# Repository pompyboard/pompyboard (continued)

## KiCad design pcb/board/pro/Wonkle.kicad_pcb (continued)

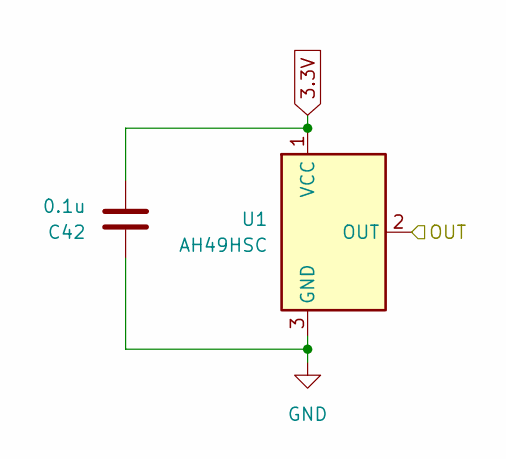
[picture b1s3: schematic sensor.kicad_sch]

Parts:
C42: 0.1u; C_0402_1005Metric; LCSC Part # C1525
U1: AH49HSC; SOT-23-3; LCSC Part # C510723

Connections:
3.3V: C42.2, U1.1 (VCC); also elsewhere on the board
/sensor column0/sensor0/OUT: U1.2 (OUT); also elsewhere on the board
GND: C42.1, U1.3 (GND); also elsewhere on the board

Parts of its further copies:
C43, C44, C45, C46, C47, C48, C49, C50, C51, C52, C53, C54, C55, C56, C57, C58, C59, C60, C61, C62, C63, C64, C65, C66, C67, C68, C69, C70, C71, C72, C73, C74, C75, C76, C77, C78, C79, C80, C81, C82, C83, C84, C85, C86, C87, C88, C89, C90, C91, C92, C93, C94, C95, C96, C97, C98, C99, C100, C101, C102, C103, C104, C105, C106, C107, C108, C109, C110, C111, C112, C113, C114, C115, C116, C117, C118, C119, C120, C121, C122, C123, C124, C125, C126, C127, C128, C129, C130, C131, C132, C133, C134, C135, C136, C137, C138, C139, C140, C141, C142, C143, C144, C145, C146, C147, C148, C149, C150, C151, C152, C153, C154, C155, C156, C157, C158, C159, C160, C161, C162, C163, C164, C165, C166, C167, C168, C169, C170, C171, C172, C173, C174, C175, C176, C177, C178, C179, C180, C181, C182, C183, C184, C185, C186, C187, C188, C189, C190, C191, C192, C193, C194, C195, C196, C197, C198, C199, C200, C201, C202, C203, C204, C205, C206, C207, C208, C209, C210, C211, C212, C213, C214, C215, C216, C217, C218, C219, C220, C221, C222, C223, C224, C225, C226, C227, C228, C229, C230, C231, C232, C233, C234, C235, C236, C237, C238, C239, C240, C241, C242, C243, C244, C245, C246, C247, C248, C249, C250: 0.1u; C_0402_1005Metric; LCSC Part # C1525
U2, U3, U4, U5, U6, U7, U8, U9, U10, U11, U12, U13, U14, U15, U16, U17, U18, U19, U20, U21, U22, U23, U24, U25, U26, U27, U28, U29, U30, U31, U32, U33, U34, U35, U36, U37, U38, U39, U40, U41, U42, U43, U44, U45, U46, U47, U48, U49, U50, U51, U52, U53, U54, U55, U56, U57, U58, U59, U60, U61, U62, U63, U64, U65, U66, U67, U68, U69, U70, U71, U72, U73, U74, U75, U76, U77, U78, U79, U80, U81, U82, U83, U84, U85, U86, U87, U88, U89, U90, U91, U92, U93, U94, U95, U96, U97, U98, U99, U100, U101, U102, U103, U104, U105, U106, U107, U108, U109, U110, U111, U112, U113, U114, U115, U116, U117, U118, U119, U120, U121, U122, U123, U124, U125, U126, U127, U128, U129, U130, U131, U132, U133, U134, U135, U136, U137, U138, U139, U140, U141, U142, U143, U144, U145, U146, U147, U148, U149, U150, U151, U152, U153, U154, U155, U156, U157, U158, U159, U160, U161, U162, U163, U164, U165, U166, U167, U168, U169, U170, U171, U172, U173, U174, U175, U176, U177, U178, U179, U180, U181, U182, U183, U184, U185, U186, U187, U188, U189, U190, U191, U192, U193, U194, U195, U196, U197, U198, U199, U200, U201, U202, U203, U204, U205, U206, U207, U208, U209: AH49HSC; SOT-23-3; LCSC Part # C510723

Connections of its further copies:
3.3V: C43.2, C44.2, C45.2, C46.2, C47.2, C48.2, C49.2, C50.2, C51.2, C52.2, C53.2, C54.2, C55.2, C56.2, C57.2, C58.2, C59.2, C60.2, C61.2, C62.2, C63.2, C64.2, C65.2, C66.2, C67.2, C68.2, C69.2, C70.2, C71.2, C72.2, C73.2, C74.2, C75.2, C76.2, C77.2, C78.2, C79.2, C80.2, C81.2, C82.2, C83.2, C84.2, C85.2, C86.2, C87.2, C88.2, C89.2, C90.2, C91.2, C92.2, C93.2, C94.2, C95.2, C96.2, C97.2, C98.2, C99.2, C100.2, C101.2, C102.2, C103.2, C104.2, C105.2, C106.2, C107.2, C108.2, C109.2, C110.2, C111.2, C112.2, C113.2, C114.2, C115.2, C116.2, C117.2, C118.2, C119.2, C120.2, C121.2, C122.2, C123.2, C124.2, C125.2, C126.2, C127.2, C128.2, C129.2, C130.2, C131.2, C132.2, C133.2, C134.2, C135.2, C136.2, C137.2, C138.2, C139.2, C140.2, C141.2, C142.2, C143.2, C144.2, C145.2, C146.2, C147.2, C148.2, C149.2, C150.2, C151.2, C152.2, C153.2, C154.2, C155.2, C156.2, C157.2, C158.2, C159.2, C160.2, C161.2, C162.2, C163.2, C164.2, C165.2, C166.2, C167.2, C168.2, C169.2, C170.2, C171.2, C172.2, C173.2, C174.2, C175.2, C176.2, C177.2, C178.2, C179.2, C180.2, C181.2, C182.2, C183.2, C184.2, C185.2, C186.2, C187.2, C188.2, C189.2, C190.2, C191.2, C192.2, C193.2, C194.2, C195.2, C196.2, C197.2, C198.2, C199.2, C200.2, C201.2, C202.2, C203.2, C204.2, C205.2, C206.2, C207.2, C208.2, C209.2, C210.2, C211.2, C212.2, C213.2, C214.2, C215.2, C216.2, C217.2, C218.2, C219.2, C220.2, C221.2, C222.2, C223.2, C224.2, C225.2, C226.2, C227.2, C228.2, C229.2, C230.2, C231.2, C232.2, C233.2, C234.2, C235.2, C236.2, C237.2, C238.2, C239.2, C240.2, C241.2, C242.2, C243.2, C244.2, C245.2, C246.2, C247.2, C248.2, C249.2, C250.2, U2.1 (VCC), U3.1 (VCC), U4.1 (VCC), U5.1 (VCC), U6.1 (VCC), U7.1 (VCC), U8.1 (VCC), U9.1 (VCC), U10.1 (VCC), U11.1 (VCC), U12.1 (VCC), U13.1 (VCC), U14.1 (VCC), U15.1 (VCC), U16.1 (VCC), U17.1 (VCC), U18.1 (VCC), U19.1 (VCC), U20.1 (VCC), U21.1 (VCC), U22.1 (VCC), U23.1 (VCC), U24.1 (VCC), U25.1 (VCC), U26.1 (VCC), U27.1 (VCC), U28.1 (VCC), U29.1 (VCC), U30.1 (VCC), U31.1 (VCC), U32.1 (VCC), U33.1 (VCC), U34.1 (VCC), U35.1 (VCC), U36.1 (VCC), U37.1 (VCC), U38.1 (VCC), U39.1 (VCC), U40.1 (VCC), U41.1 (VCC), U42.1 (VCC), U43.1 (VCC), U44.1 (VCC), U45.1 (VCC), U46.1 (VCC), U47.1 (VCC), U48.1 (VCC), U49.1 (VCC), U50.1 (VCC), U51.1 (VCC), U52.1 (VCC), U53.1 (VCC), U54.1 (VCC), U55.1 (VCC), U56.1 (VCC), U57.1 (VCC), U58.1 (VCC), U59.1 (VCC), U60.1 (VCC), U61.1 (VCC), U62.1 (VCC), U63.1 (VCC), U64.1 (VCC), U65.1 (VCC), U66.1 (VCC), U67.1 (VCC), U68.1 (VCC), U69.1 (VCC), U70.1 (VCC), U71.1 (VCC), U72.1 (VCC), U73.1 (VCC), U74.1 (VCC), U75.1 (VCC), U76.1 (VCC), U77.1 (VCC), U78.1 (VCC), U79.1 (VCC), U80.1 (VCC), U81.1 (VCC), U82.1 (VCC), U83.1 (VCC), U84.1 (VCC), U85.1 (VCC), U86.1 (VCC), U87.1 (VCC), U88.1 (VCC), U89.1 (VCC), U90.1 (VCC), U91.1 (VCC), U92.1 (VCC), U93.1 (VCC), U94.1 (VCC), U95.1 (VCC), U96.1 (VCC), U97.1 (VCC), U98.1 (VCC), U99.1 (VCC), U100.1 (VCC), U101.1 (VCC), U102.1 (VCC), U103.1 (VCC), U104.1 (VCC), U105.1 (VCC), U106.1 (VCC), U107.1 (VCC), U108.1 (VCC), U109.1 (VCC), U110.1 (VCC), U111.1 (VCC), U112.1 (VCC), U113.1 (VCC), U114.1 (VCC), U115.1 (VCC), U116.1 (VCC), U117.1 (VCC), U118.1 (VCC), U119.1 (VCC), U120.1 (VCC), U121.1 (VCC), U122.1 (VCC), U123.1 (VCC), U124.1 (VCC), U125.1 (VCC), U126.1 (VCC), U127.1 (VCC), U128.1 (VCC), U129.1 (VCC), U130.1 (VCC), U131.1 (VCC), U132.1 (VCC), U133.1 (VCC), U134.1 (VCC), U135.1 (VCC), U136.1 (VCC), U137.1 (VCC), U138.1 (VCC), U139.1 (VCC), U140.1 (VCC), U141.1 (VCC), U142.1 (VCC), U143.1 (VCC), U144.1 (VCC), U145.1 (VCC), U146.1 (VCC), U147.1 (VCC), U148.1 (VCC), U149.1 (VCC), U150.1 (VCC), U151.1 (VCC), U152.1 (VCC), U153.1 (VCC), U154.1 (VCC), U155.1 (VCC), U156.1 (VCC), U157.1 (VCC), U158.1 (VCC), U159.1 (VCC), U160.1 (VCC), U161.1 (VCC), U162.1 (VCC), U163.1 (VCC), U164.1 (VCC), U165.1 (VCC), U166.1 (VCC), U167.1 (VCC), U168.1 (VCC), U169.1 (VCC), U170.1 (VCC), U171.1 (VCC), U172.1 (VCC), U173.1 (VCC), U174.1 (VCC), U175.1 (VCC), U176.1 (VCC), U177.1 (VCC), U178.1 (VCC), U179.1 (VCC), U180.1 (VCC), U181.1 (VCC), U182.1 (VCC), U183.1 (VCC), U184.1 (VCC), U185.1 (VCC), U186.1 (VCC), U187.1 (VCC), U188.1 (VCC), U189.1 (VCC), U190.1 (VCC), U191.1 (VCC), U192.1 (VCC), U193.1 (VCC), U194.1 (VCC), U195.1 (VCC), U196.1 (VCC), U197.1 (VCC), U198.1 (VCC), U199.1 (VCC), U200.1 (VCC), U201.1 (VCC), U202.1 (VCC), U203.1 (VCC), U204.1 (VCC), U205.1 (VCC), U206.1 (VCC), U207.1 (VCC), U208.1 (VCC), U209.1 (VCC); also elsewhere on the board
/sensor column0/sensor1/OUT: U20.2 (OUT); also elsewhere on the board
/sensor column0/sensor2/OUT: U39.2 (OUT); also elsewhere on the board
/sensor column0/sensor3/OUT: U58.2 (OUT); also elsewhere on the board
/sensor column0/sensor4/OUT: U77.2 (OUT); also elsewhere on the board
/sensor column0/sensor5/OUT: U96.2 (OUT); also elsewhere on the board
/sensor column0/sensor6/OUT: U115.2 (OUT); also elsewhere on the board
/sensor column0/sensor7/OUT: U134.2 (OUT); also elsewhere on the board
/sensor column0/sensor8/OUT: U153.2 (OUT); also elsewhere on the board
/sensor column0/sensor9/OUT: U172.2 (OUT); also elsewhere on the board
/sensor column0/sensor10/OUT: U191.2 (OUT); also elsewhere on the board
/sensor column1/sensor0/OUT: U2.2 (OUT); also elsewhere on the board
/sensor column1/sensor1/OUT: U21.2 (OUT); also elsewhere on the board
/sensor column1/sensor2/OUT: U40.2 (OUT); also elsewhere on the board
/sensor column1/sensor3/OUT: U59.2 (OUT); also elsewhere on the board
/sensor column1/sensor4/OUT: U78.2 (OUT); also elsewhere on the board
/sensor column1/sensor5/OUT: U97.2 (OUT); also elsewhere on the board
/sensor column1/sensor6/OUT: U116.2 (OUT); also elsewhere on the board
/sensor column1/sensor7/OUT: U135.2 (OUT); also elsewhere on the board
/sensor column1/sensor8/OUT: U154.2 (OUT); also elsewhere on the board
/sensor column1/sensor9/OUT: U173.2 (OUT); also elsewhere on the board
/sensor column1/sensor10/OUT: U192.2 (OUT); also elsewhere on the board
/sensor column2/sensor0/OUT: U3.2 (OUT); also elsewhere on the board
/sensor column2/sensor1/OUT: U22.2 (OUT); also elsewhere on the board
/sensor column2/sensor2/OUT: U41.2 (OUT); also elsewhere on the board
/sensor column2/sensor3/OUT: U60.2 (OUT); also elsewhere on the board
/sensor column2/sensor4/OUT: U79.2 (OUT); also elsewhere on the board
/sensor column2/sensor5/OUT: U98.2 (OUT); also elsewhere on the board
/sensor column2/sensor6/OUT: U117.2 (OUT); also elsewhere on the board
/sensor column2/sensor7/OUT: U136.2 (OUT); also elsewhere on the board
/sensor column2/sensor8/OUT: U155.2 (OUT); also elsewhere on the board
/sensor column2/sensor9/OUT: U174.2 (OUT); also elsewhere on the board
/sensor column2/sensor10/OUT: U193.2 (OUT); also elsewhere on the board
/sensor column3/sensor0/OUT: U4.2 (OUT); also elsewhere on the board
/sensor column3/sensor1/OUT: U23.2 (OUT); also elsewhere on the board
/sensor column3/sensor2/OUT: U42.2 (OUT); also elsewhere on the board
/sensor column3/sensor3/OUT: U61.2 (OUT); also elsewhere on the board
/sensor column3/sensor4/OUT: U80.2 (OUT); also elsewhere on the board
/sensor column3/sensor5/OUT: U99.2 (OUT); also elsewhere on the board
/sensor column3/sensor6/OUT: U118.2 (OUT); also elsewhere on the board
/sensor column3/sensor7/OUT: U137.2 (OUT); also elsewhere on the board
/sensor column3/sensor8/OUT: U156.2 (OUT); also elsewhere on the board
/sensor column3/sensor9/OUT: U175.2 (OUT); also elsewhere on the board
/sensor column3/sensor10/OUT: U194.2 (OUT); also elsewhere on the board
/sensor column4/sensor0/OUT: U5.2 (OUT); also elsewhere on the board
/sensor column4/sensor1/OUT: U24.2 (OUT); also elsewhere on the board
/sensor column4/sensor2/OUT: U43.2 (OUT); also elsewhere on the board
/sensor column4/sensor3/OUT: U62.2 (OUT); also elsewhere on the board
/sensor column4/sensor4/OUT: U81.2 (OUT); also elsewhere on the board
/sensor column4/sensor5/OUT: U100.2 (OUT); also elsewhere on the board
/sensor column4/sensor6/OUT: U119.2 (OUT); also elsewhere on the board
/sensor column4/sensor7/OUT: U138.2 (OUT); also elsewhere on the board
/sensor column4/sensor8/OUT: U157.2 (OUT); also elsewhere on the board
/sensor column4/sensor9/OUT: U176.2 (OUT); also elsewhere on the board
/sensor column4/sensor10/OUT: U195.2 (OUT); also elsewhere on the board
/sensor column5/sensor0/OUT: U6.2 (OUT); also elsewhere on the board
/sensor column5/sensor1/OUT: U25.2 (OUT); also elsewhere on the board
/sensor column5/sensor2/OUT: U44.2 (OUT); also elsewhere on the board
/sensor column5/sensor3/OUT: U63.2 (OUT); also elsewhere on the board
/sensor column5/sensor4/OUT: U82.2 (OUT); also elsewhere on the board
/sensor column5/sensor5/OUT: U101.2 (OUT); also elsewhere on the board
/sensor column5/sensor6/OUT: U120.2 (OUT); also elsewhere on the board
/sensor column5/sensor7/OUT: U139.2 (OUT); also elsewhere on the board
/sensor column5/sensor8/OUT: U158.2 (OUT); also elsewhere on the board
/sensor column5/sensor9/OUT: U177.2 (OUT); also elsewhere on the board
/sensor column5/sensor10/OUT: U196.2 (OUT); also elsewhere on the board
/sensor column6/sensor0/OUT: U7.2 (OUT); also elsewhere on the board
/sensor column6/sensor1/OUT: U26.2 (OUT); also elsewhere on the board
/sensor column6/sensor2/OUT: U45.2 (OUT); also elsewhere on the board
/sensor column6/sensor3/OUT: U64.2 (OUT); also elsewhere on the board
/sensor column6/sensor4/OUT: U83.2 (OUT); also elsewhere on the board
/sensor column6/sensor5/OUT: U102.2 (OUT); also elsewhere on the board
/sensor column6/sensor6/OUT: U121.2 (OUT); also elsewhere on the board
/sensor column6/sensor7/OUT: U140.2 (OUT); also elsewhere on the board
/sensor column6/sensor8/OUT: U159.2 (OUT); also elsewhere on the board
/sensor column6/sensor9/OUT: U178.2 (OUT); also elsewhere on the board
/sensor column6/sensor10/OUT: U197.2 (OUT); also elsewhere on the board
/sensor column7/sensor0/OUT: U8.2 (OUT); also elsewhere on the board
/sensor column7/sensor1/OUT: U27.2 (OUT); also elsewhere on the board
/sensor column7/sensor2/OUT: U46.2 (OUT); also elsewhere on the board
/sensor column7/sensor3/OUT: U65.2 (OUT); also elsewhere on the board
/sensor column7/sensor4/OUT: U84.2 (OUT); also elsewhere on the board
/sensor column7/sensor5/OUT: U103.2 (OUT); also elsewhere on the board
/sensor column7/sensor6/OUT: U122.2 (OUT); also elsewhere on the board
/sensor column7/sensor7/OUT: U141.2 (OUT); also elsewhere on the board
/sensor column7/sensor8/OUT: U160.2 (OUT); also elsewhere on the board
/sensor column7/sensor9/OUT: U179.2 (OUT); also elsewhere on the board
/sensor column7/sensor10/OUT: U198.2 (OUT); also elsewhere on the board
/sensor column8/sensor0/OUT: U9.2 (OUT); also elsewhere on the board
/sensor column8/sensor1/OUT: U28.2 (OUT); also elsewhere on the board
/sensor column8/sensor2/OUT: U47.2 (OUT); also elsewhere on the board
/sensor column8/sensor3/OUT: U66.2 (OUT); also elsewhere on the board
/sensor column8/sensor4/OUT: U85.2 (OUT); also elsewhere on the board
/sensor column8/sensor5/OUT: U104.2 (OUT); also elsewhere on the board
/sensor column8/sensor6/OUT: U123.2 (OUT); also elsewhere on the board
/sensor column8/sensor7/OUT: U142.2 (OUT); also elsewhere on the board
/sensor column8/sensor8/OUT: U161.2 (OUT); also elsewhere on the board
/sensor column8/sensor9/OUT: U180.2 (OUT); also elsewhere on the board
/sensor column8/sensor10/OUT: U199.2 (OUT); also elsewhere on the board
/sensor column9/sensor0/OUT: U10.2 (OUT); also elsewhere on the board
/sensor column9/sensor1/OUT: U29.2 (OUT); also elsewhere on the board
/sensor column9/sensor2/OUT: U48.2 (OUT); also elsewhere on the board
/sensor column9/sensor3/OUT: U67.2 (OUT); also elsewhere on the board
/sensor column9/sensor4/OUT: U86.2 (OUT); also elsewhere on the board
/sensor column9/sensor5/OUT: U105.2 (OUT); also elsewhere on the board
/sensor column9/sensor6/OUT: U124.2 (OUT); also elsewhere on the board
/sensor column9/sensor7/OUT: U143.2 (OUT); also elsewhere on the board
/sensor column9/sensor8/OUT: U162.2 (OUT); also elsewhere on the board
/sensor column9/sensor9/OUT: U181.2 (OUT); also elsewhere on the board
/sensor column9/sensor10/OUT: U200.2 (OUT); also elsewhere on the board
/sensor column10/sensor0/OUT: U11.2 (OUT); also elsewhere on the board
/sensor column10/sensor1/OUT: U30.2 (OUT); also elsewhere on the board
/sensor column10/sensor2/OUT: U49.2 (OUT); also elsewhere on the board
/sensor column10/sensor3/OUT: U68.2 (OUT); also elsewhere on the board
/sensor column10/sensor4/OUT: U87.2 (OUT); also elsewhere on the board
/sensor column10/sensor5/OUT: U106.2 (OUT); also elsewhere on the board
/sensor column10/sensor6/OUT: U125.2 (OUT); also elsewhere on the board
/sensor column10/sensor7/OUT: U144.2 (OUT); also elsewhere on the board
/sensor column10/sensor8/OUT: U163.2 (OUT); also elsewhere on the board
/sensor column10/sensor9/OUT: U182.2 (OUT); also elsewhere on the board
/sensor column10/sensor10/OUT: U201.2 (OUT); also elsewhere on the board
/sensor column11/sensor0/OUT: U12.2 (OUT); also elsewhere on the board
/sensor column11/sensor1/OUT: U31.2 (OUT); also elsewhere on the board
/sensor column11/sensor2/OUT: U50.2 (OUT); also elsewhere on the board
/sensor column11/sensor3/OUT: U69.2 (OUT); also elsewhere on the board
/sensor column11/sensor4/OUT: U88.2 (OUT); also elsewhere on the board
/sensor column11/sensor5/OUT: U107.2 (OUT); also elsewhere on the board
/sensor column11/sensor6/OUT: U126.2 (OUT); also elsewhere on the board
/sensor column11/sensor7/OUT: U145.2 (OUT); also elsewhere on the board
/sensor column11/sensor8/OUT: U164.2 (OUT); also elsewhere on the board
/sensor column11/sensor9/OUT: U183.2 (OUT); also elsewhere on the board
/sensor column11/sensor10/OUT: U202.2 (OUT); also elsewhere on the board
/sensor column12/sensor0/OUT: U13.2 (OUT); also elsewhere on the board
/sensor column12/sensor1/OUT: U32.2 (OUT); also elsewhere on the board
/sensor column12/sensor2/OUT: U51.2 (OUT); also elsewhere on the board
/sensor column12/sensor3/OUT: U70.2 (OUT); also elsewhere on the board
/sensor column12/sensor4/OUT: U89.2 (OUT); also elsewhere on the board
/sensor column12/sensor5/OUT: U108.2 (OUT); also elsewhere on the board
/sensor column12/sensor6/OUT: U127.2 (OUT); also elsewhere on the board
/sensor column12/sensor7/OUT: U146.2 (OUT); also elsewhere on the board
/sensor column12/sensor8/OUT: U165.2 (OUT); also elsewhere on the board
/sensor column12/sensor9/OUT: U184.2 (OUT); also elsewhere on the board
/sensor column12/sensor10/OUT: U203.2 (OUT); also elsewhere on the board
/sensor column13/sensor0/OUT: U14.2 (OUT); also elsewhere on the board
/sensor column13/sensor1/OUT: U33.2 (OUT); also elsewhere on the board
/sensor column13/sensor2/OUT: U52.2 (OUT); also elsewhere on the board
/sensor column13/sensor3/OUT: U71.2 (OUT); also elsewhere on the board
/sensor column13/sensor4/OUT: U90.2 (OUT); also elsewhere on the board
/sensor column13/sensor5/OUT: U109.2 (OUT); also elsewhere on the board
/sensor column13/sensor6/OUT: U128.2 (OUT); also elsewhere on the board
/sensor column13/sensor7/OUT: U147.2 (OUT); also elsewhere on the board
/sensor column13/sensor8/OUT: U166.2 (OUT); also elsewhere on the board
/sensor column13/sensor9/OUT: U185.2 (OUT); also elsewhere on the board
/sensor column13/sensor10/OUT: U204.2 (OUT); also elsewhere on the board
/sensor column14/sensor0/OUT: U15.2 (OUT); also elsewhere on the board
/sensor column14/sensor1/OUT: U34.2 (OUT); also elsewhere on the board
/sensor column14/sensor2/OUT: U53.2 (OUT); also elsewhere on the board
/sensor column14/sensor3/OUT: U72.2 (OUT); also elsewhere on the board
/sensor column14/sensor4/OUT: U91.2 (OUT); also elsewhere on the board
/sensor column14/sensor5/OUT: U110.2 (OUT); also elsewhere on the board
/sensor column14/sensor6/OUT: U129.2 (OUT); also elsewhere on the board
/sensor column14/sensor7/OUT: U148.2 (OUT); also elsewhere on the board
/sensor column14/sensor8/OUT: U167.2 (OUT); also elsewhere on the board
/sensor column14/sensor9/OUT: U186.2 (OUT); also elsewhere on the board
/sensor column14/sensor10/OUT: U205.2 (OUT); also elsewhere on the board
/sensor column15/sensor0/OUT: U16.2 (OUT); also elsewhere on the board
/sensor column15/sensor1/OUT: U35.2 (OUT); also elsewhere on the board
/sensor column15/sensor2/OUT: U54.2 (OUT); also elsewhere on the board
/sensor column15/sensor3/OUT: U73.2 (OUT); also elsewhere on the board
/sensor column15/sensor4/OUT: U92.2 (OUT); also elsewhere on the board
/sensor column15/sensor5/OUT: U111.2 (OUT); also elsewhere on the board
/sensor column15/sensor6/OUT: U130.2 (OUT); also elsewhere on the board
/sensor column15/sensor7/OUT: U149.2 (OUT); also elsewhere on the board
/sensor column15/sensor8/OUT: U168.2 (OUT); also elsewhere on the board
/sensor column15/sensor9/OUT: U187.2 (OUT); also elsewhere on the board
/sensor column15/sensor10/OUT: U206.2 (OUT); also elsewhere on the board
/sensor column16/sensor0/OUT: U17.2 (OUT); also elsewhere on the board
/sensor column16/sensor1/OUT: U36.2 (OUT); also elsewhere on the board
/sensor column16/sensor2/OUT: U55.2 (OUT); also elsewhere on the board
/sensor column16/sensor3/OUT: U74.2 (OUT); also elsewhere on the board
/sensor column16/sensor4/OUT: U93.2 (OUT); also elsewhere on the board
/sensor column16/sensor5/OUT: U112.2 (OUT); also elsewhere on the board
/sensor column16/sensor6/OUT: U131.2 (OUT); also elsewhere on the board
/sensor column16/sensor7/OUT: U150.2 (OUT); also elsewhere on the board
/sensor column16/sensor8/OUT: U169.2 (OUT); also elsewhere on the board
/sensor column16/sensor9/OUT: U188.2 (OUT); also elsewhere on the board
/sensor column16/sensor10/OUT: U207.2 (OUT); also elsewhere on the board
/sensor column17/sensor0/OUT: U18.2 (OUT); also elsewhere on the board
/sensor column17/sensor1/OUT: U37.2 (OUT); also elsewhere on the board
/sensor column17/sensor2/OUT: U56.2 (OUT); also elsewhere on the board
/sensor column17/sensor3/OUT: U75.2 (OUT); also elsewhere on the board
/sensor column17/sensor4/OUT: U94.2 (OUT); also elsewhere on the board
/sensor column17/sensor5/OUT: U113.2 (OUT); also elsewhere on the board
/sensor column17/sensor6/OUT: U132.2 (OUT); also elsewhere on the board
/sensor column17/sensor7/OUT: U151.2 (OUT); also elsewhere on the board
/sensor column17/sensor8/OUT: U170.2 (OUT); also elsewhere on the board
/sensor column17/sensor9/OUT: U189.2 (OUT); also elsewhere on the board
/sensor column17/sensor10/OUT: U208.2 (OUT); also elsewhere on the board
/sensor column18/sensor0/OUT: U19.2 (OUT); also elsewhere on the board
/sensor column18/sensor1/OUT: U38.2 (OUT); also elsewhere on the board
/sensor column18/sensor2/OUT: U57.2 (OUT); also elsewhere on the board
/sensor column18/sensor3/OUT: U76.2 (OUT); also elsewhere on the board
/sensor column18/sensor4/OUT: U95.2 (OUT); also elsewhere on the board
/sensor column18/sensor5/OUT: U114.2 (OUT); also elsewhere on the board
/sensor column18/sensor6/OUT: U133.2 (OUT); also elsewhere on the board
/sensor column18/sensor7/OUT: U152.2 (OUT); also elsewhere on the board
/sensor column18/sensor8/OUT: U171.2 (OUT); also elsewhere on the board
/sensor column18/sensor9/OUT: U190.2 (OUT); also elsewhere on the board
/sensor column18/sensor10/OUT: U209.2 (OUT); also elsewhere on the board
GND: C43.1, C44.1, C45.1, C46.1, C47.1, C48.1, C49.1, C50.1, C51.1, C52.1, C53.1, C54.1, C55.1, C56.1, C57.1, C58.1, C59.1, C60.1, C61.1, C62.1, C63.1, C64.1, C65.1, C66.1, C67.1, C68.1, C69.1, C70.1, C71.1, C72.1, C73.1, C74.1, C75.1, C76.1, C77.1, C78.1, C79.1, C80.1, C81.1, C82.1, C83.1, C84.1, C85.1, C86.1, C87.1, C88.1, C89.1, C90.1, C91.1, C92.1, C93.1, C94.1, C95.1, C96.1, C97.1, C98.1, C99.1, C100.1, C101.1, C102.1, C103.1, C104.1, C105.1, C106.1, C107.1, C108.1, C109.1, C110.1, C111.1, C112.1, C113.1, C114.1, C115.1, C116.1, C117.1, C118.1, C119.1, C120.1, C121.1, C122.1, C123.1, C124.1, C125.1, C126.1, C127.1, C128.1, C129.1, C130.1, C131.1, C132.1, C133.1, C134.1, C135.1, C136.1, C137.1, C138.1, C139.1, C140.1, C141.1, C142.1, C143.1, C144.1, C145.1, C146.1, C147.1, C148.1, C149.1, C150.1, C151.1, C152.1, C153.1, C154.1, C155.1, C156.1, C157.1, C158.1, C159.1, C160.1, C161.1, C162.1, C163.1, C164.1, C165.1, C166.1, C167.1, C168.1, C169.1, C170.1, C171.1, C172.1, C173.1, C174.1, C175.1, C176.1, C177.1, C178.1, C179.1, C180.1, C181.1, C182.1, C183.1, C184.1, C185.1, C186.1, C187.1, C188.1, C189.1, C190.1, C191.1, C192.1, C193.1, C194.1, C195.1, C196.1, C197.1, C198.1, C199.1, C200.1, C201.1, C202.1, C203.1, C204.1, C205.1, C206.1, C207.1, C208.1, C209.1, C210.1, C211.1, C212.1, C213.1, C214.1, C215.1, C216.1, C217.1, C218.1, C219.1, C220.1, C221.1, C222.1, C223.1, C224.1, C225.1, C226.1, C227.1, C228.1, C229.1, C230.1, C231.1, C232.1, C233.1, C234.1, C235.1, C236.1, C237.1, C238.1, C239.1, C240.1, C241.1, C242.1, C243.1, C244.1, C245.1, C246.1, C247.1, C248.1, C249.1, C250.1, U2.3 (GND), U3.3 (GND), U4.3 (GND), U5.3 (GND), U6.3 (GND), U7.3 (GND), U8.3 (GND), U9.3 (GND), U10.3 (GND), U11.3 (GND), U12.3 (GND), U13.3 (GND), U14.3 (GND), U15.3 (GND), U16.3 (GND), U17.3 (GND), U18.3 (GND), U19.3 (GND), U20.3 (GND), U21.3 (GND), U22.3 (GND), U23.3 (GND), U24.3 (GND), U25.3 (GND), U26.3 (GND), U27.3 (GND), U28.3 (GND), U29.3 (GND), U30.3 (GND), U31.3 (GND), U32.3 (GND), U33.3 (GND), U34.3 (GND), U35.3 (GND), U36.3 (GND), U37.3 (GND), U38.3 (GND), U39.3 (GND), U40.3 (GND), U41.3 (GND), U42.3 (GND), U43.3 (GND), U44.3 (GND), U45.3 (GND), U46.3 (GND), U47.3 (GND), U48.3 (GND), U49.3 (GND), U50.3 (GND), U51.3 (GND), U52.3 (GND), U53.3 (GND), U54.3 (GND), U55.3 (GND), U56.3 (GND), U57.3 (GND), U58.3 (GND), U59.3 (GND), U60.3 (GND), U61.3 (GND), U62.3 (GND), U63.3 (GND), U64.3 (GND), U65.3 (GND), U66.3 (GND), U67.3 (GND), U68.3 (GND), U69.3 (GND), U70.3 (GND), U71.3 (GND), U72.3 (GND), U73.3 (GND), U74.3 (GND), U75.3 (GND), U76.3 (GND), U77.3 (GND), U78.3 (GND), U79.3 (GND), U80.3 (GND), U81.3 (GND), U82.3 (GND), U83.3 (GND), U84.3 (GND), U85.3 (GND), U86.3 (GND), U87.3 (GND), U88.3 (GND), U89.3 (GND), U90.3 (GND), U91.3 (GND), U92.3 (GND), U93.3 (GND), U94.3 (GND), U95.3 (GND), U96.3 (GND), U97.3 (GND), U98.3 (GND), U99.3 (GND), U100.3 (GND), U101.3 (GND), U102.3 (GND), U103.3 (GND), U104.3 (GND), U105.3 (GND), U106.3 (GND), U107.3 (GND), U108.3 (GND), U109.3 (GND), U110.3 (GND), U111.3 (GND), U112.3 (GND), U113.3 (GND), U114.3 (GND), U115.3 (GND), U116.3 (GND), U117.3 (GND), U118.3 (GND), U119.3 (GND), U120.3 (GND), U121.3 (GND), U122.3 (GND), U123.3 (GND), U124.3 (GND), U125.3 (GND), U126.3 (GND), U127.3 (GND), U128.3 (GND), U129.3 (GND), U130.3 (GND), U131.3 (GND), U132.3 (GND), U133.3 (GND), U134.3 (GND), U135.3 (GND), U136.3 (GND), U137.3 (GND), U138.3 (GND), U139.3 (GND), U140.3 (GND), U141.3 (GND), U142.3 (GND), U143.3 (GND), U144.3 (GND), U145.3 (GND), U146.3 (GND), U147.3 (GND), U148.3 (GND), U149.3 (GND), U150.3 (GND), U151.3 (GND), U152.3 (GND), U153.3 (GND), U154.3 (GND), U155.3 (GND), U156.3 (GND), U157.3 (GND), U158.3 (GND), U159.3 (GND), U160.3 (GND), U161.3 (GND), U162.3 (GND), U163.3 (GND), U164.3 (GND), U165.3 (GND), U166.3 (GND), U167.3 (GND), U168.3 (GND), U169.3 (GND), U170.3 (GND), U171.3 (GND), U172.3 (GND), U173.3 (GND), U174.3 (GND), U175.3 (GND), U176.3 (GND), U177.3 (GND), U178.3 (GND), U179.3 (GND), U180.3 (GND), U181.3 (GND), U182.3 (GND), U183.3 (GND), U184.3 (GND), U185.3 (GND), U186.3 (GND), U187.3 (GND), U188.3 (GND), U189.3 (GND), U190.3 (GND), U191.3 (GND), U192.3 (GND), U193.3 (GND), U194.3 (GND), U195.3 (GND), U196.3 (GND), U197.3 (GND), U198.3 (GND), U199.3 (GND), U200.3 (GND), U201.3 (GND), U202.3 (GND), U203.3 (GND), U204.3 (GND), U205.3 (GND), U206.3 (GND), U207.3 (GND), U208.3 (GND), U209.3 (GND); also elsewhere on the board

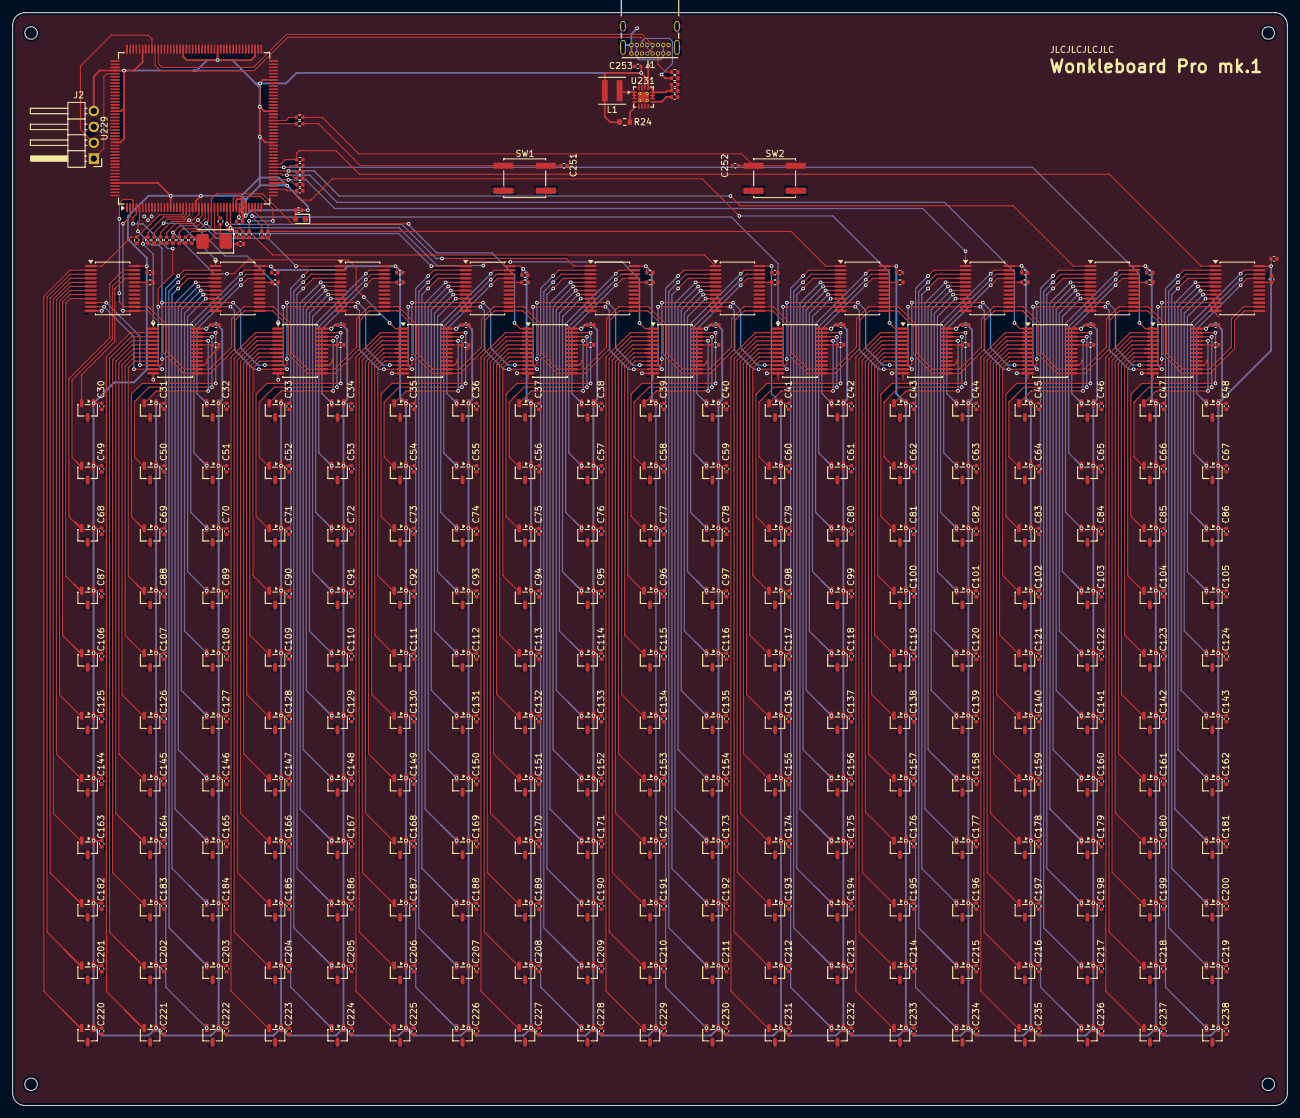
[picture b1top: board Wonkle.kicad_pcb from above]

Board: 2 copper layers, 204.0 x 174.9 mm, 519 parts (0 on the bottom side), 271 nets.

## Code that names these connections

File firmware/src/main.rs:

#![allow(static_mut_refs)]
#![no_main]
#![no_std]

mod crc16;
mod profiler;
mod sensor;
mod tablet;
mod telemetry;
mod usb;

use defmt_rtt as _;
// See https://defmt.ferrous-systems.com/global-logger for more information
use panic_probe as _; // Print panic message to probe console
use stm32f4xx_hal::{otg_fs, pac, prelude::*, rcc::Config};

const USB_ENUMERATION_DELAY_MS: u32 = 3000;

#[cortex_m_rt::entry]
fn main() -> ! {
    defmt::info!("Hello from Wonkle!");

    let dp = pac::Peripherals::take().unwrap(); // device peripheral
    let mut cp = cortex_m::peripheral::Peripherals::take().unwrap(); // core peripheral
    let mut rcc = dp.RCC.freeze(
        Config::hsi()
            .sysclk(84.MHz()) // HCLK
            .pclk1(42.MHz()) // APB1
            .pclk2(84.MHz()) // APB2
            .require_pll48clk(), // PLL
    );

    profiler::enable_cycle_counter(&mut cp.DCB, &mut cp.DWT);

    let gpioa = dp.GPIOA.split(&mut rcc);
    let gpioc = dp.GPIOC.split(&mut rcc);
    let gpioe = dp.GPIOE.split(&mut rcc);
    let gpiof = dp.GPIOF.split(&mut rcc);

    // sensor input pins
    let _ = gpioa.pa1.into_analog();
    let _ = gpioa.pa2.into_analog();
    let _ = gpioa.pa3.into_analog();
    let _ = gpioa.pa4.into_analog();
    let _ = gpioa.pa6.into_analog();
    let _ = gpioa.pa7.into_analog();
    let _ = gpioc.pc1.into_analog();
    let _ = gpioc.pc2.into_analog();
    let _ = gpioc.pc3.into_analog();
    let _ = gpioc.pc4.into_analog();
    let _ = gpioc.pc5.into_analog();
    let _ = gpiof.pf3.into_analog();
    let _ = gpiof.pf4.into_analog();
    let _ = gpiof.pf5.into_analog();
    let _ = gpiof.pf6.into_analog();
    let _ = gpiof.pf7.into_analog();
    let _ = gpiof.pf8.into_analog();
    let _ = gpiof.pf9.into_analog();
    let _ = gpiof.pf10.into_analog();

    let mux: sensor::MuxSelect = (
        gpioe.pe6.into_push_pull_output(),
        gpioe.pe5.into_push_pull_output(),
        gpioe.pe4.into_push_pull_output(),
        gpioe.pe3.into_push_pull_output(),
    )
        .outport();

    let usb_peripheral = otg_fs::USB::new(
        (dp.OTG_FS_GLOBAL, dp.OTG_FS_DEVICE, dp.OTG_FS_PWRCLK),
        (gpioa.pa11, gpioa.pa12),
        &rcc.clocks,
    );

    defmt::info!(
        "Waiting {}ms for USB enumeration...",
        USB_ENUMERATION_DELAY_MS
    );
    cp.SYST
        .delay(&rcc.clocks)
        .delay_ms(USB_ENUMERATION_DELAY_MS);

    defmt::info!("Initializing...");
    let mut usb_device = usb::build(usb_peripheral);
    let mut sensor_grid = sensor::SensorGrid::new(dp.ADC2, dp.ADC3, mux, &mut rcc);
    let mut profiler = profiler::PerformanceProfiler::new(rcc.clocks.sysclk().raw());
    profiler.init();
    let mut telemetry = telemetry::Telemetry::new();
    let mut tablet = tablet::Tablet::new();
    let mut grid_buffer = [0u16; sensor::SENSOR_COUNT];

    defmt::info!("Initialized!");
    defmt::info!(
        "Config: mux_settling={}, adc_sampling={}, re_reads={}",
        sensor_grid.mux_settling(),
        sensor::adc_sampling_label(sensor_grid.adc_sampling()),
        sensor_grid.adc_re_reads()
    );
    defmt::info!(
        "Filters: ema_alpha_per_mille={}",
        sensor_grid.ema_alpha() * 1000.0
    );

    loop {
        profiler.begin(true);

        // Pump USB first so CDC RX is fresh for the host commands, then dispatch any commands.
        usb_device.poll();
        telemetry.service(&mut usb_device, &mut sensor_grid, &profiler);
        profiler.mark_telemetry_service();

        sensor_grid.scan_grid(&mut grid_buffer);
        profiler.mark_scan();
        profiler.record_scan_details(sensor_grid.last_scan_timing());

        let mut cursor = tablet.find_centroid(&grid_buffer);
        profiler.mark_centroid();

        tablet.update_cursor(&sensor_grid, &mut cursor, &usb_device);
        profiler.mark_usb();
        profiler.report_if_due();

        telemetry.feed_grid(
            &grid_buffer,
            cursor.x,
            cursor.y,
            cursor.valid,
            &mut usb_device,
        );
    }
}

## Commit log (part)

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2025-10-19 Added several pen models
2025-10-19 fixed magnet dimensions
2025-11-02 fix: Update text for clarity and improve layout in mk.1 Lite and Pro pages
2025-11-02 Initial plan
2025-11-02 chore(web): run Prettier formatting
2025-11-02 Convex works kinda
2025-11-02 web: added convex rules for copilot
2025-11-02 fix: update tsconfig.json formatting for better readability
2025-11-02 Web refactor: structure and comments for clarity
2025-11-02 made the whole mailing list work with convex, also the tsconfig gets changed due to prettier
2025-11-02 rebased
2025-11-03 web: fix nav link not working outside of homepage
2025-11-03 web: add Home link to navbar for completeness
2025-11-03 web: remove redundant tailwind classes
2025-11-03 web: be more conservative with shadows on smaller cards
2025-11-03 web: entire shop item card jumping on hover feels bad
2025-11-03 web: make shop item card animation feel snappier
2025-11-03 web: make "All products" button actually bring users to product list
2025-11-03 web: make spacing look better on "All products" button
2025-11-03 web: remove new tab icons where they're not important
2025-11-03 web: show full list of products in comparison section so it's easier to parse
2025-11-03 web: make shadow size look better
2025-11-03 web: better text
2025-11-04 web: revert speeding up of shimmer effect
2025-11-04 web: add aria-label for accessibility
2025-11-04 remove devenv stuff from Web CI
2025-11-06 testing new push rule
2025-11-06 split CI by scope
2025-11-06 Remove AI prompts from PR as requested
2025-11-06 Homepage touchup (#9)
    * web: remove new tab icons where they're not important
    * web: show full list of products in comparison section so it's easier to parse
    * web: make shadow size look better
    * web: better text
2025-11-06 Use pnpx instead of npx in env example
2025-11-06 Update README and use t3 env for environment variables
2025-11-06 Remove example value comments from schema.ts
2025-11-08 remove technology page (will be replaced by better description of product and an actual documentation)
2025-11-08 web: fix hallucinated config
2025-11-08 web: remove drizzle (replaced with convex)
2025-11-08 web: make .env.local.example the canonical example env file
2025-11-08 web: we don't need tutorial files in our codebase that will get outdated in a few months
2025-11-08 web: prevent mailing list section appearing twice and make source attribute more type-safe
2025-11-08 web: remove comment that serves the same purpose as README
2025-11-08 update cSpell dictionary
2025-11-09 web: do convex codegen before building nextjs site
2025-11-09 web: remove unused db stuff (they belong in another PR)
2025-11-09 code cleanup
2025-11-09 web: remove unused dependency
2025-11-09 web: remove unused file
2025-11-09 web: replace npm-run-all with concurrently
2025-11-09 web: use convex's rate limiting solution
2025-11-09 disable waitlist for now
2025-11-09 fix failing CI
2025-11-09 web: ignore generated files when formatting
2025-11-09 vscode: prevent editing generated files
2025-11-09 web: make eslint track deprecated APIs
2025-11-09 remove BRANDING.md (will be replaced with branding page on the website)
2025-11-09 remove comparison that's already in the website
2025-11-09 rebrand from Pompyboard to Wonkle
2025-11-22 web: added wonkle text with pronunciation button
2025-11-22 web: consistent icon, button and footer refactored
2025-11-22 web: removed unnecessary footer files
2025-11-22 web: type removed from button
2025-11-22 web: update wonkle pronunciation audio file
2025-11-22 web: correct formatting
2025-11-22 fix pronunciation button making unnecessary network requests
2025-11-22 fix rebase fuckery
2025-12-15 FAQ Updates
2025-12-15 Removed a question that was already handled at the beginning of the FAQ
2025-12-15 Revised FAQ
2025-12-16 improve formatting
2025-12-17 Revisions based on pomp's feedback
2025-12-18 docs: apply formatting and fix grammatical error
2026-02-08 hex experimental test
2026-02-12 Initial pre-recorded data positioning algorithm analyzer
2026-02-12 minors
2026-05-29 Added HSE oscilator circuit and footprint mismatch fix
    fixed previous DRC footprint mismatch error, Updated project to KiCAD 10, added 8Mhz XTAL for HSE for reliable USB polling, Renamed project files to Wonkle
2026-05-29 Remove Old Pompyboard files
2026-06-26 firmware v0.1 baseline ported to rust from cpp
2026-06-26 align cspell.yaml
